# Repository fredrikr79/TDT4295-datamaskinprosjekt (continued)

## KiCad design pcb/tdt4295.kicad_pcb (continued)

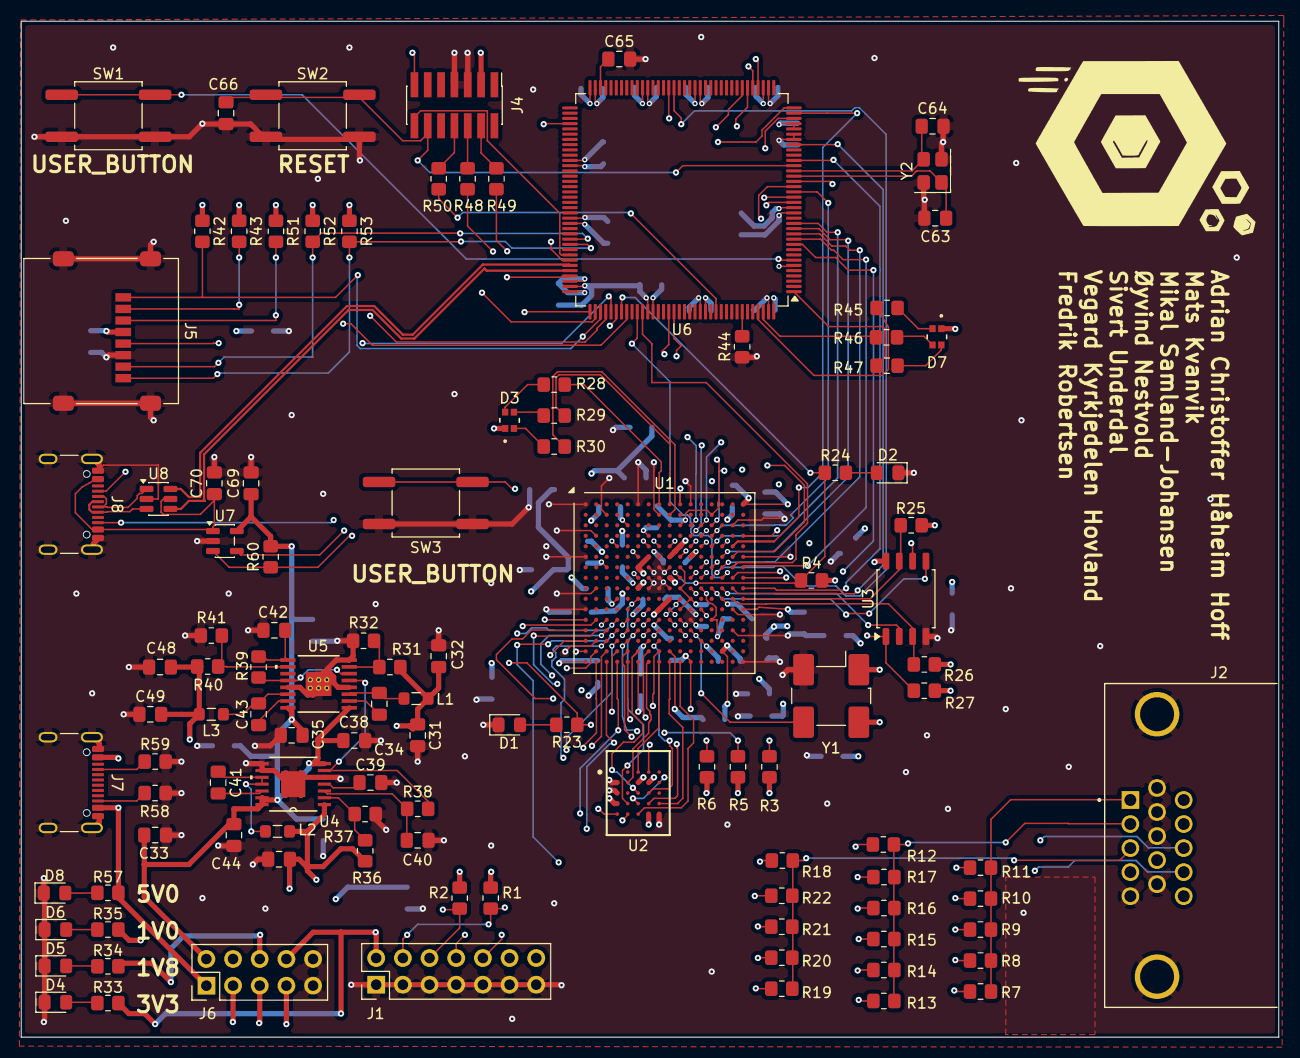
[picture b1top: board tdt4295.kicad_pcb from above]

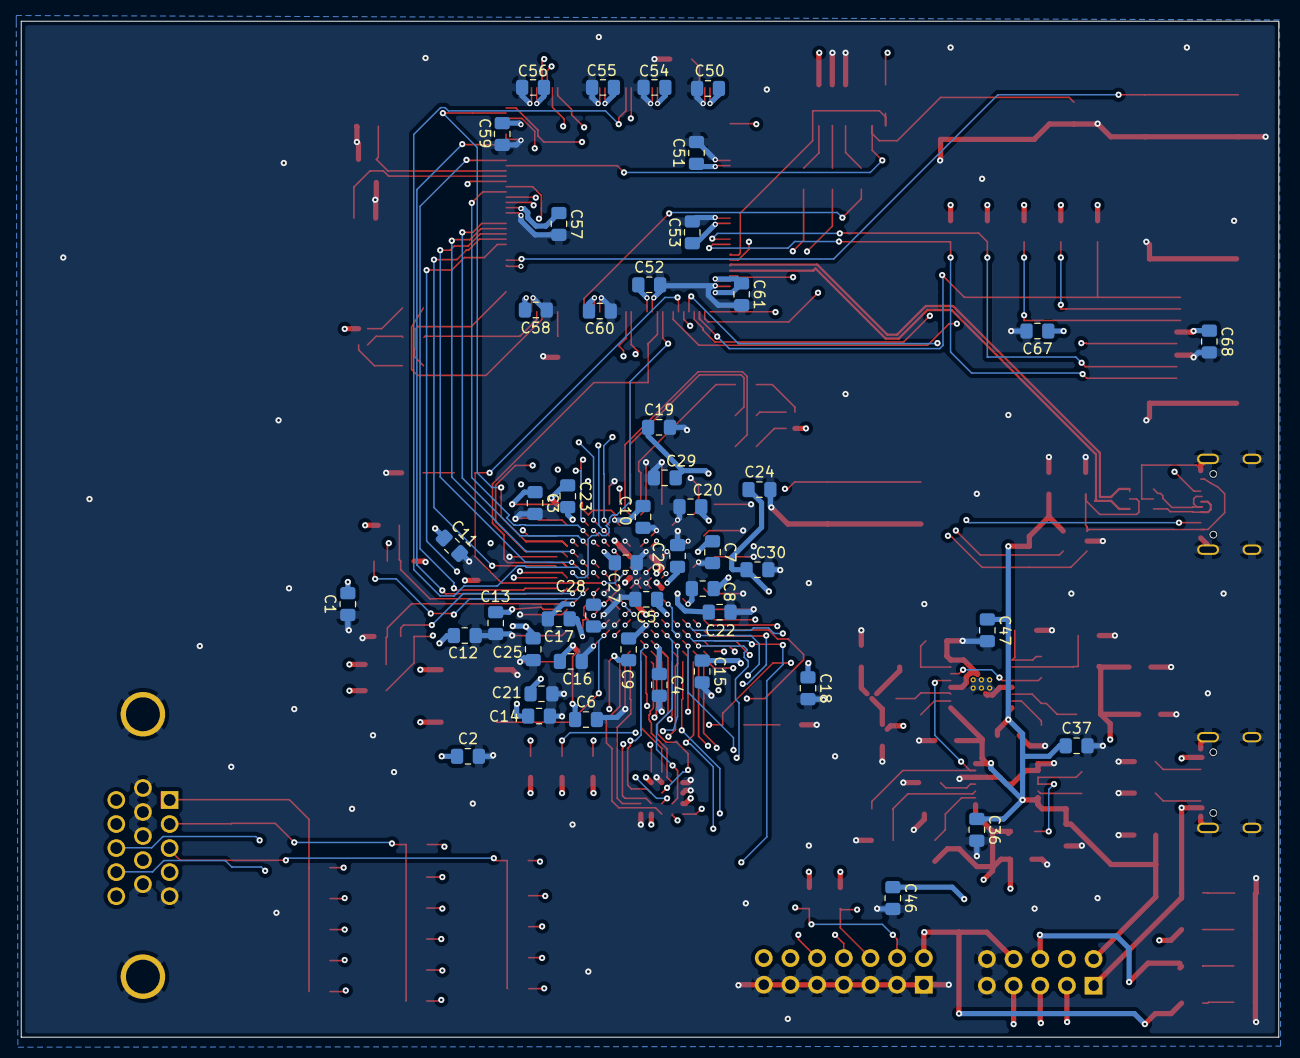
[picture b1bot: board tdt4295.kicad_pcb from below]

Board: 6 copper layers, 119.8 x 96.8 mm, 157 parts (48 on the bottom side), 144 nets.

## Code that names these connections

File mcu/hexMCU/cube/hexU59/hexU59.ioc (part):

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Mcu.Name=STM32U595ZJTx
Mcu.Package=LQFP144
Mcu.UserName=STM32U595ZJTx
PA10.Mode=Asynchronous
PA10.Signal=USART1_RX
PA2.Mode=OCTOSPI1_Port1_NCS
PA2.Signal=OCTOSPIM_P1_NCS
PA4.GPIOParameters=GPIO_Label
PA4.GPIO_Label=Drive_VBUS
PA4.Signal=GPIO_Output
PA5.GPIOParameters=GPIO_PuPd,GPIO_Label
PA5.GPIO_Label=fault_signal
PA5.GPIO_PuPd=GPIO_PULLUP
PA5.Signal=GPIO_Input
PA9.Mode=Asynchronous
PA9.Signal=USART1_TX
PC0.Mode=OCTOSPI1_IOH_Port1H
PC0.Signal=OCTOSPIM_P1_IO7
PC10.Mode=SD_4_bits_Wide_bus
PC10.Signal=SDMMC1_D2
PC11.Mode=SD_4_bits_Wide_bus
PC11.Signal=SDMMC1_D3
PC12.Mode=SD_4_bits_Wide_bus
PC12.Signal=SDMMC1_CK
PC13.GPIOParameters=GPIO_PuPd,GPIO_Label,GPIO_ModeDefaultEXTI
PC13.GPIO_Label=USER_BUTTON
PC13.GPIO_ModeDefaultEXTI=GPIO_MODE_IT_FALLING
PC13.GPIO_PuPd=GPIO_PULLUP
PC13.Signal=GPXTI13
PC3.Mode=OCTOSPI1_IOH_Port1H
PC3.Signal=OCTOSPIM_P1_IO6
PC8.Mode=SD_4_bits_Wide_bus
PC8.Signal=SDMMC1_D0
PC9.Mode=SD_4_bits_Wide_bus
PC9.Signal=SDMMC1_D1
PD0.GPIOParameters=PinState,GPIO_PuPd,GPIO_Label,GPIO_ModeDefaultOutputPP
PD0.GPIO_Label=FPGA_PROGRAM_B
PD0.GPIO_ModeDefaultOutputPP=GPIO_MODE_OUTPUT_OD
PD0.GPIO_PuPd=GPIO_NOPULL
PD0.PinState=GPIO_PIN_SET
PD0.Signal=GPIO_Output
PD1.GPIOParameters=GPIO_Label
PD1.GPIO_Label=FPGA_DONE
PD1.Signal=GPIO_Input
PD2.Mode=SD_4_bits_Wide_bus
PD2.Signal=SDMMC1_CMD
PD4.Mode=OCTOSPI1_IOH_Port1H
PD4.Signal=OCTOSPIM_P1_IO4
PD5.Mode=OCTOSPI1_IOH_Port1H
PD5.Signal=OCTOSPIM_P1_IO5
PE0.GPIOParameters=PinState,GPIO_Label
PE0.GPIO_Label=LED_B
PE0.PinState=GPIO_PIN_SET
PE0.Signal=GPIO_Output
PE1.GPIOParameters=PinState,GPIO_Label
PE1.GPIO_Label=LED_G
PE1.PinState=GPIO_PIN_SET
PE1.Signal=GPIO_Output
PE2.GPIOParameters=PinState,GPIO_Label
PE2.GPIO_Label=LED_R
PE2.PinState=GPIO_PIN_SET
PE2.Signal=GPIO_Output
PF0.GPIOParameters=GPIO_PuPd,GPIO_Label
PF0.GPIO_Label=FPGA_READY
PF0.GPIO_PuPd=GPIO_PULLDOWN
PF0.Signal=GPXTI0
PF1.GPIOParameters=GPIO_PuPd,GPIO_Label
PF1.GPIO_Label=FPGA_ACK
PF1.GPIO_PuPd=GPIO_PULLDOWN
PF1.Signal=GPIO_Input
PF10.Mode=O1_P1_CLK
PF10.Signal=OCTOSPIM_P1_CLK
PF2.GPIOParameters=GPIO_PuPd,GPIO_Label
PF2.GPIO_Label=FPGA_SYNC
PF2.GPIO_PuPd=GPIO_PULLDOWN
PF2.Signal=GPXTI2
PF3.GPIOParameters=GPIO_Speed,PinState,GPIO_Label
PF3.GPIO_Label=FPGA_RESET
PF3.GPIO_Speed=GPIO_SPEED_FREQ_HIGH
PF3.PinState=GPIO_PIN_SET
PF3.Signal=GPIO_Output
PF6.Mode=OCTOSPI1_IOL_Port1L
PF6.Signal=OCTOSPIM_P1_IO3
PF7.Mode=OCTOSPI1_IOL_Port1L
PF7.Signal=OCTOSPIM_P1_IO2
PF8.Mode=OCTOSPI1_IOL_Port1L
PF8.Signal=OCTOSPIM_P1_IO0
PF9.Mode=OCTOSPI1_IOL_Port1L
PF9.Signal=OCTOSPIM_P1_IO1
PH0-OSC_IN\ (PH0).Mode=HSE-External-Oscillator
PH0-OSC_IN\ (PH0).Signal=RCC_OSC_IN
PH1-OSC_OUT\ (PH1).Mode=HSE-External-Oscillator
PH1-OSC_OUT\ (PH1).Signal=RCC_OSC_OUT
RCC.HSE_VALUE=16000000
RCC.SYSCLKFreq_VALUE=160000000
RCC.SYSCLKSource=RCC_SYSCLKSOURCE_PLLCLK
board=custom

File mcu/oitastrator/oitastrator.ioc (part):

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Mcu.Name=STM32U545RETxQ
Mcu.Package=LQFP64
Mcu.UserName=STM32U545RETxQ
PA0.GPIOParameters=GPIO_PuPd,GPIO_Speed_High_Default
PA0.GPIO_PuPd=GPIO_PULLUP
PA0.GPIO_Speed_High_Default=GPIO_SPEED_FREQ_HIGH
PA0.Mode=octo_mode
PA0.Signal=OCTOSPI1_NCS
PA1.GPIOParameters=GPIO_Speed
PA1.GPIO_Speed=GPIO_SPEED_FREQ_VERY_HIGH
PA1.Mode=Full_Duplex_Master
PA1.Signal=SPI1_SCK
PA10.Mode=Asynchronous
PA10.Signal=USART1_RX
PA11.GPIOParameters=GPIO_Speed
PA11.GPIO_Speed=GPIO_SPEED_FREQ_VERY_HIGH
PA11.Mode=Full_Duplex_Master
PA11.Signal=SPI1_MISO
PA12.GPIOParameters=GPIO_Speed
PA12.GPIO_Speed=GPIO_SPEED_FREQ_VERY_HIGH
PA12.Mode=Full_Duplex_Master
PA12.Signal=SPI1_MOSI
PA3.GPIOParameters=GPIO_PuPd,GPIO_Speed_High_Default
PA3.GPIO_PuPd=GPIO_NOPULL
PA3.GPIO_Speed_High_Default=GPIO_SPEED_FREQ_HIGH
PA3.Mode=octo_mode
PA3.Signal=OCTOSPI1_CLK
PA4.GPIOParameters=GPIO_PuPd,GPIO_Label
PA4.GPIO_Label=FPGA_READY
PA4.GPIO_PuPd=GPIO_PULLDOWN
PA4.Signal=GPXTI4
PA5.GPIOParameters=GPIO_Label
PA5.GPIO_Label=LED_GREEN
PA5.Signal=GPIO_Output
PA6.GPIOParameters=GPIO_Speed_High_Default
PA6.GPIO_Speed_High_Default=GPIO_SPEED_FREQ_HIGH
PA6.Mode=octo_mode
PA6.Signal=OCTOSPI1_IO3
PA7.GPIOParameters=GPIO_Speed_High_Default
PA7.GPIO_Speed_High_Default=GPIO_SPEED_FREQ_HIGH
PA7.Mode=octo_mode
PA7.Signal=OCTOSPI1_IO2
PA9.Mode=Asynchronous
PA9.Signal=USART1_TX
PB0.GPIOParameters=GPIO_Speed_High_Default
PB0.GPIO_Speed_High_Default=GPIO_SPEED_FREQ_HIGH
PB0.Mode=octo_mode
PB0.Signal=OCTOSPI1_IO1
PB1.GPIOParameters=GPIO_Speed_High_Default
PB1.GPIO_Speed_High_Default=GPIO_SPEED_FREQ_HIGH
PB1.Mode=octo_mode
PB1.Signal=OCTOSPI1_IO0
PB10.GPIOParameters=GPIO_Label
PB10.GPIO_Label=FPGA_ACK
PB10.Signal=LPGPIO_Input
PC0.GPIOParameters=GPIO_Speed_High_Default
PC0.GPIO_Speed_High_Default=GPIO_SPEED_FREQ_HIGH
PC0.Mode=octo_mode
PC0.Signal=OCTOSPI1_IO7
PC1.GPIOParameters=GPIO_Speed_High_Default
PC1.GPIO_Speed_High_Default=GPIO_SPEED_FREQ_HIGH
PC1.Mode=octo_mode
PC1.Signal=OCTOSPI1_IO4
PC13.Signal=GPIO_Input
PC14-OSC32_IN\ (PC14).Mode=LSE-External-Oscillator
PC14-OSC32_IN\ (PC14).Signal=RCC_OSC32_IN
PC15-OSC32_OUT\ (PC15).Mode=LSE-External-Oscillator
PC15-OSC32_OUT\ (PC15).Signal=RCC_OSC32_OUT
PC2.GPIOParameters=GPIO_Speed_High_Default
PC2.GPIO_Speed_High_Default=GPIO_SPEED_FREQ_HIGH
PC2.Mode=octo_mode
PC2.Signal=OCTOSPI1_IO5
PC3.GPIOParameters=GPIO_Speed_High_Default
PC3.GPIO_Speed_High_Default=GPIO_SPEED_FREQ_HIGH
PC3.Mode=octo_mode
PC3.Signal=OCTOSPI1_IO6
RCC.HSE_VALUE=16000000
RCC.SYSCLKFreq_VALUE=160000000
RCC.SYSCLKSource=RCC_SYSCLKSOURCE_PLLCLK
board=custom
